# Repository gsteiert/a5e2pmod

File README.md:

# A MicroSD and PMOD adapter for the Agilex 5 E-Series Premium Devkit

## Schematic

[View the schematic online in KiCanvas](https://kicanvas.org/?github=https%3A%2F%2Fgithub.com%2Fgsteiert%2Fa5e2pmod%2Fblob%2Fmain%2Fa5e2pmod.kicad_sch)

## Pinout

|  Agilex 5         |  J9  |  PMOD  |  Micro SD  |
| ----------------- | ---- | ------ | ---------- |
|  3.3V             |  1   |  11,12 | 4 VDD      |
|  BU31  HVIO_6A_5  |  2   |  1     | 2 DAT3/CD  |
|  BU28  HVIO_6A_1  |  3   |  2     | 8 DAT1     |
|  BM28  HVIO_6A_6  |  4   |  3     | 3 CMD      |
|  BP31  HVIO_6A_2  |  5   |  4     | 1 DAT2     |
|  BF21  HVIO_6B_1  |  6   |  5     | 7 DAT0     |
|  BR28  HVIO_6A_3  |  7   |  6     | 9 DET      |
|  BM31  HVIO_6A_8  |  8   |  7     | 5 CLK      |
|  BR31  HVIO_6A_4  |  9   |  8     | -          |
|  GND              |  10  |  9,10  | 6 VSS      |

## PMOD

## Installed

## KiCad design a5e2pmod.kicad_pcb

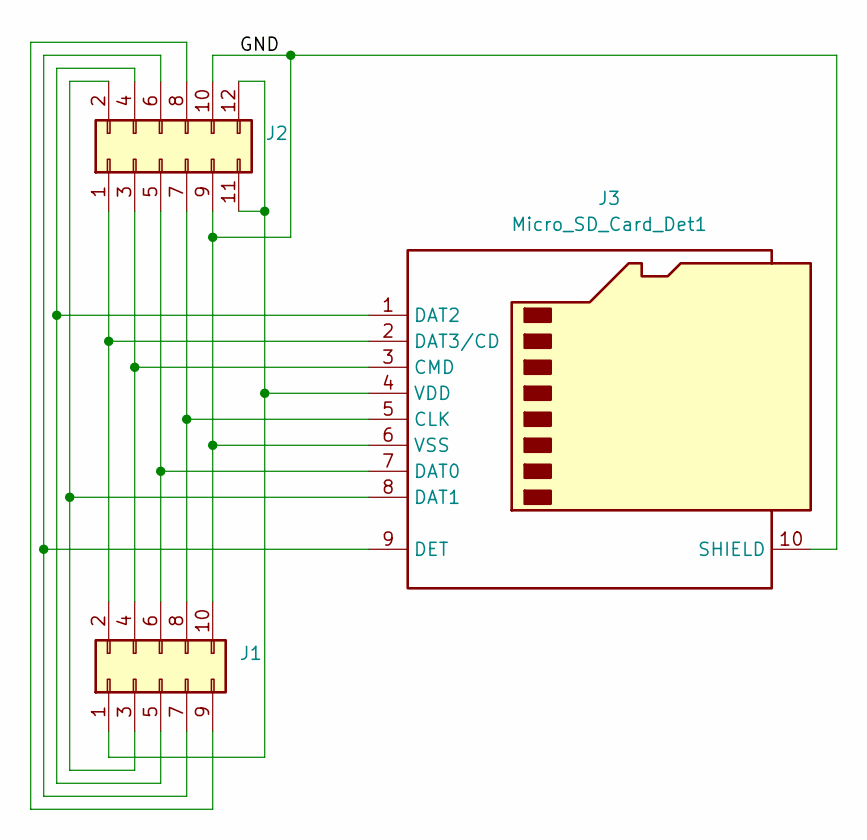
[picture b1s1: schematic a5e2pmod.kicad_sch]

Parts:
J1: Conn_02x05_Odd_Even; PinSocket_2x05_P2.54mm_Horizontal
J2: Conn_02x06_Odd_Even; PMOD_Hybrid
J3: Micro_SD_Card_Det1; 105162-0001_MOL

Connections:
/GND: J1.10, J2.9, J2.10, J3.6 (VSS), J3.10 (SHIELD)
unnamed: J1.1, J2.11, J2.12, J3.4 (VDD)
unnamed: J1.2, J2.1, J3.2 (DAT3/CD)
unnamed: J1.3, J2.2, J3.8 (DAT1)
unnamed: J1.4, J2.3, J3.3 (CMD)
unnamed: J1.5, J2.4, J3.1 (DAT2)
unnamed: J1.6, J2.5, J3.7 (DAT0)
unnamed: J1.7, J2.6, J3.9 (DET)
unnamed: J1.8, J2.7, J3.5 (CLK)
unnamed: J1.9, J2.8

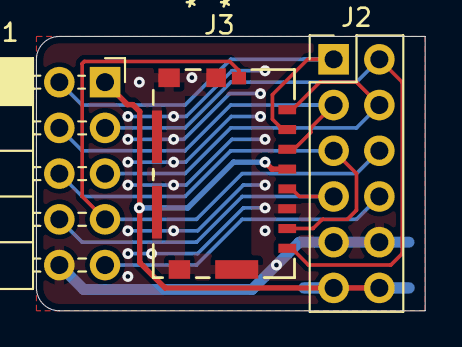
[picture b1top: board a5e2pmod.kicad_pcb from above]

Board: 2 copper layers, 21.6 x 15.2 mm, 3 parts (0 on the bottom side), 10 nets.

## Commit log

2024-07-17 added link to KiCanvas schematic
2024-07-18 adding pmod pinout diagram and installed picture
